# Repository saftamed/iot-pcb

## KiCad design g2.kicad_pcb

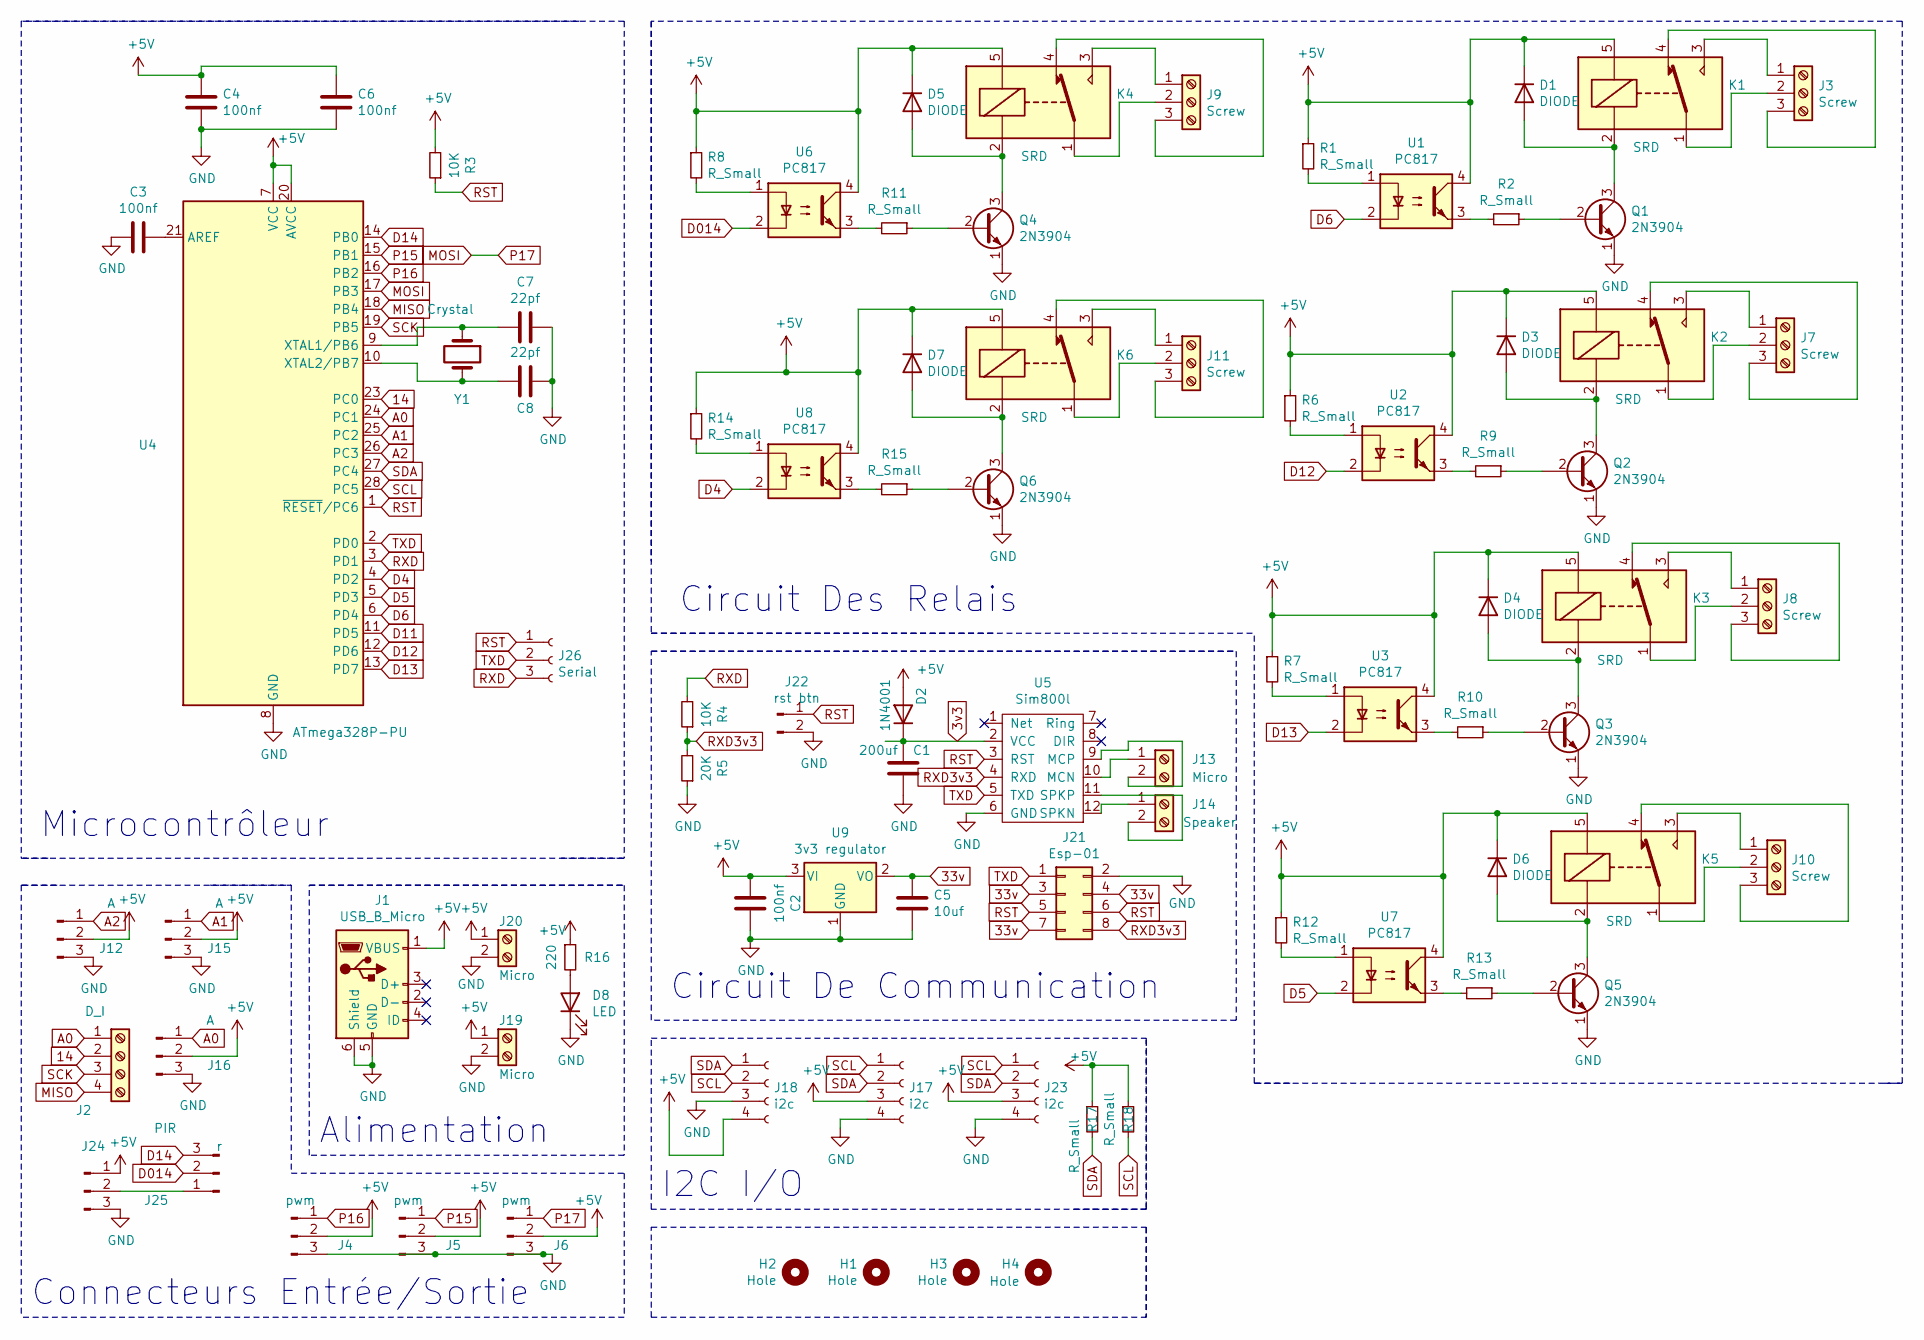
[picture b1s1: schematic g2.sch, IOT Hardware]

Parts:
C1: 200uf; CP_Radial_D5.0mm_P2.50mm
C2, C3, C4, C6: 100nf; C_Disc_D5.0mm_W2.5mm_P2.50mm
C5: 10uf; CP_Radial_D5.0mm_P2.50mm
C7, C8: 22pf; C_Disc_D5.0mm_W2.5mm_P2.50mm
D1, D3, D4, D5, D6, D7: DIODE; D_DO-41_SOD81_P7.62mm_Horizontal
D2: 1N4001; D_DO-41_SOD81_P7.62mm_Horizontal
D8: LED; LED_D3.0mm
H1, H2, H3, H4: Hole; MountingHole_2.7mm_M2.5_Pad_Via
J1: USB_B_Micro; USB_Micro-B_Molex_47346-0001
J2: D_I; TerminalBlock_bornier-4_P5.08mm
J3, J7, J8, J9, J10, J11: Screw; TerminalBlock_bornier-3_P5.08mm
J4, J5, J6: pwm; PinHeader_1x03_P2.54mm_Vertical
J12, J15, J16: A; PinHeader_1x03_P2.54mm_Vertical
J13, J19, J20: Micro; TerminalBlock_bornier-2_P5.08mm
J14: Speaker; TerminalBlock_bornier-2_P5.08mm
J17, J18, J23: i2c; PinSocket_1x04_P2.54mm_Vertical
J21: Esp-01; PinSocket_2x04_P2.54mm_Vertical
J22: rst btn; PinHeader_1x02_P2.54mm_Vertical
J24: PIR; PinHeader_1x03_P2.54mm_Vertical
J25: r; PinHeader_1x03_P2.54mm_Vertical
J26: Serial; PinSocket_1x03_P2.54mm_Vertical
K1, K2, K3, K4, K5, K6: SRD; Relay_SPDT_SANYOU_SRD_Series_Form_C
Q1, Q2, Q3, Q4, Q5, Q6: 2N3904; TO-92_Inline
R1, R2, R6, R7, R8, R9, R10, R11, R12, R13, R14, R15, R17, R18: R_Small; R_Axial_DIN0204_L3.6mm_D1.6mm_P5.08mm_Horizontal
R3, R4: 10K; R_Axial_DIN0204_L3.6mm_D1.6mm_P5.08mm_Horizontal
R5: 20K; R_Axial_DIN0204_L3.6mm_D1.6mm_P5.08mm_Horizontal
R16: 220; R_Axial_DIN0204_L3.6mm_D1.6mm_P5.08mm_Horizontal
U1, U2, U3, U6, U7, U8: PC817; DIP-4_W7.62mm
U4: ATmega328P-PU; DIP-28_W7.62mm
U5: Sim800l; sim800l
U9: 3v3 regulator; SOT-223-3_TabPin2
Y1: Crystal; Crystal_HC18-U_Vertical

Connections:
3v3: C1.1, D2.1 (K), U5.2 (VCC)
14: J2.2, U4.23 (PC0)
33v: C5.1, J21.3, J21.4, J21.7, U9.2 (VO)
+5V: C2.2, C4.1, C6.1, D1.2 (K), D2.2 (A), D3.2 (K), D4.2 (K), D5.2 (K), D6.2 (K), D7.2 (K), J1.1 (VBUS), J4.2, J5.2, J6.2, J12.2, J15.2, J16.2, J17.3, J18.4, J19.1, J20.1, J23.3, J24.1, K1.5, K2.5, K3.5, K4.5, K5.5, K6.5, R1.1, R3.2, R6.1, R7.1, R8.1, R12.1, R14.1, R16.1, R17.1, R18.1, U1.4, U2.4, U3.4, U4.7 (VCC), U4.20 (AVCC), U6.4, U7.4, U8.4, U9.3 (VI); also elsewhere on the board
A0: J2.1, J16.1, U4.24 (PC1)
A1: J15.1, U4.25 (PC2)
A2: J12.1, U4.26 (PC3)
D4: U4.4 (PD2), U8.2
D5: U4.5 (PD3), U7.2
D6: U1.2, U4.6 (PD4)
D11: U4.11 (PD5)
D12: U2.2, U4.12 (PD6)
D13: U3.2, U4.13 (PD7)
D014: J25.2, U6.2
D14: J25.3, U4.14 (PB0)
GND: C1.2, C2.1, C3.2, C4.2, C5.2, C6.2, C7.1, C8.1, D8.1 (K), J1.5 (GND), J1.6 (Shield), J4.3, J5.3, J6.3, J12.3, J15.3, J16.3, J17.4, J18.3, J19.2, J20.2, J21.2, J22.2, J23.4, J24.3, Q1.1 (E), Q2.1 (E), Q3.1 (E), Q4.1 (E), Q5.1 (E), Q6.1 (E), R5.1, U4.8 (GND), U4.22 (GND), U5.6 (GND), U9.1 (GND); also elsewhere on the board
MISO: J2.4, U4.18 (PB4)
MOSI: J6.1, U4.17 (PB3)
unnamed: C3.1, U4.21 (AREF)
unnamed: C7.2, U4.9 (XTAL1/PB6), Y1.1
unnamed: C8.2, U4.10 (XTAL2/PB7), Y1.2
unnamed: D1.1 (A), K1.2, Q1.3 (C)
unnamed: D3.1 (A), K2.2, Q2.3 (C)
unnamed: D4.1 (A), K3.2, Q3.3 (C)
unnamed: D5.1 (A), K4.2, Q4.3 (C)
unnamed: D6.1 (A), K5.2, Q5.3 (C)
unnamed: D7.1 (A), K6.2, Q6.3 (C)
unnamed: D8.2 (A), R16.2
unnamed: J3.1, K1.3
unnamed: J3.2, K1.1
unnamed: J3.3, K1.4
unnamed: J7.1, K2.3
unnamed: J7.2, K2.1
unnamed: J7.3, K2.4
unnamed: J8.1, K3.3
unnamed: J8.2, K3.1
unnamed: J8.3, K3.4
unnamed: J9.1, K4.3
unnamed: J9.2, K4.1
unnamed: J9.3, K4.4
unnamed: J10.1, K5.3
unnamed: J10.2, K5.1
unnamed: J10.3, K5.4
unnamed: J11.1, K6.3
unnamed: J11.2, K6.1
unnamed: J11.3, K6.4
unnamed: J13.1, U5.10 (MCN)
unnamed: J13.2, U5.9 (MCP)
unnamed: J14.1, U5.12 (SPKN)
unnamed: J14.2, U5.11 (SPKP)
unnamed: J24.2, J25.1
unnamed: Q1.2 (B), R2.1
unnamed: Q2.2 (B), R9.1
unnamed: Q3.2 (B), R10.1
unnamed: Q4.2 (B), R11.1
unnamed: Q5.2 (B), R13.1
unnamed: Q6.2 (B), R15.1
unnamed: R1.2, U1.1
unnamed: R2.2, U1.3
unnamed: R6.2, U2.1
unnamed: R7.2, U3.1
unnamed: R8.2, U6.1
unnamed: R9.2, U2.3
unnamed: R10.2, U3.3
unnamed: R11.2, U6.3
unnamed: R12.2, U7.1
unnamed: R13.2, U7.3
unnamed: R14.2, U8.1
unnamed: R15.2, U8.3
P15: J5.1, U4.15 (PB1)
P16: J4.1, U4.16 (PB2)
RST: J21.5, J21.6, J22.1, J26.1, R3.1, U4.1 (~RESET~/PC6), U5.3 (RST)
RXD: J26.3, R4.2, U4.3 (PD1)
RXD3v3: J21.8, R4.1, R5.2, U5.4 (RXD)
SCK: J2.3, U4.19 (PB5)
SCL: J17.1, J18.2, J23.1, R18.2, U4.28 (PC5); also elsewhere on the board
SDA: J17.2, J18.1, J23.2, R17.2, U4.27 (PC4); also elsewhere on the board
TXD: J21.1, J26.2, U4.2 (PD0), U5.5 (TXD)

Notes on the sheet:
Connecteurs Entrée/Sortie
Alimentation
I2C I/O
Circuit De Communication
Circuit Des Relais
Microcontrôleur

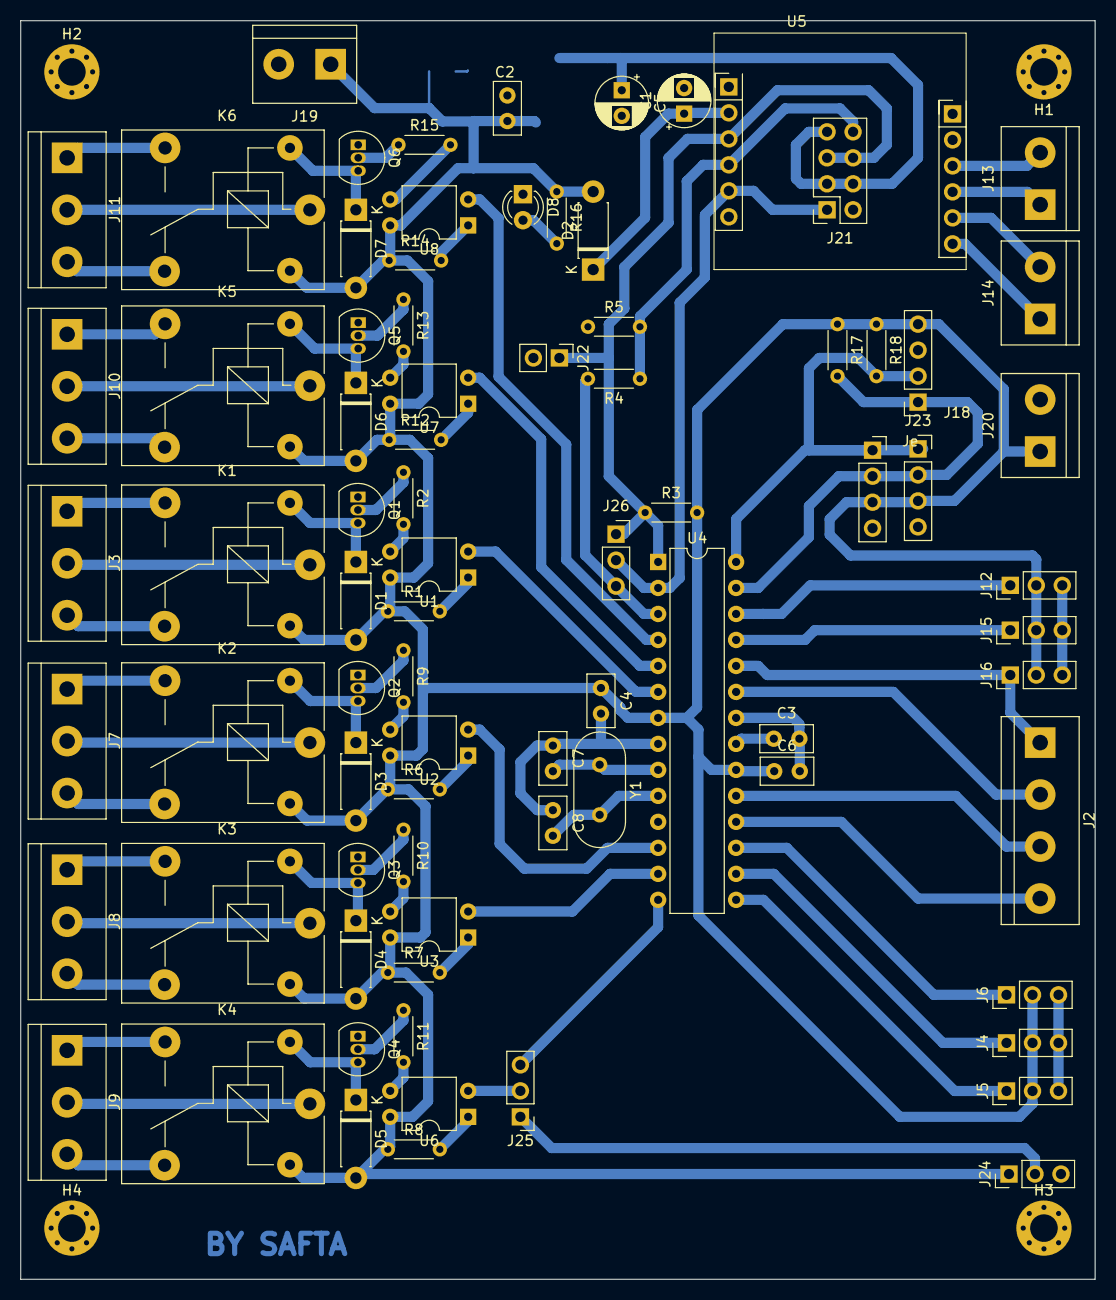
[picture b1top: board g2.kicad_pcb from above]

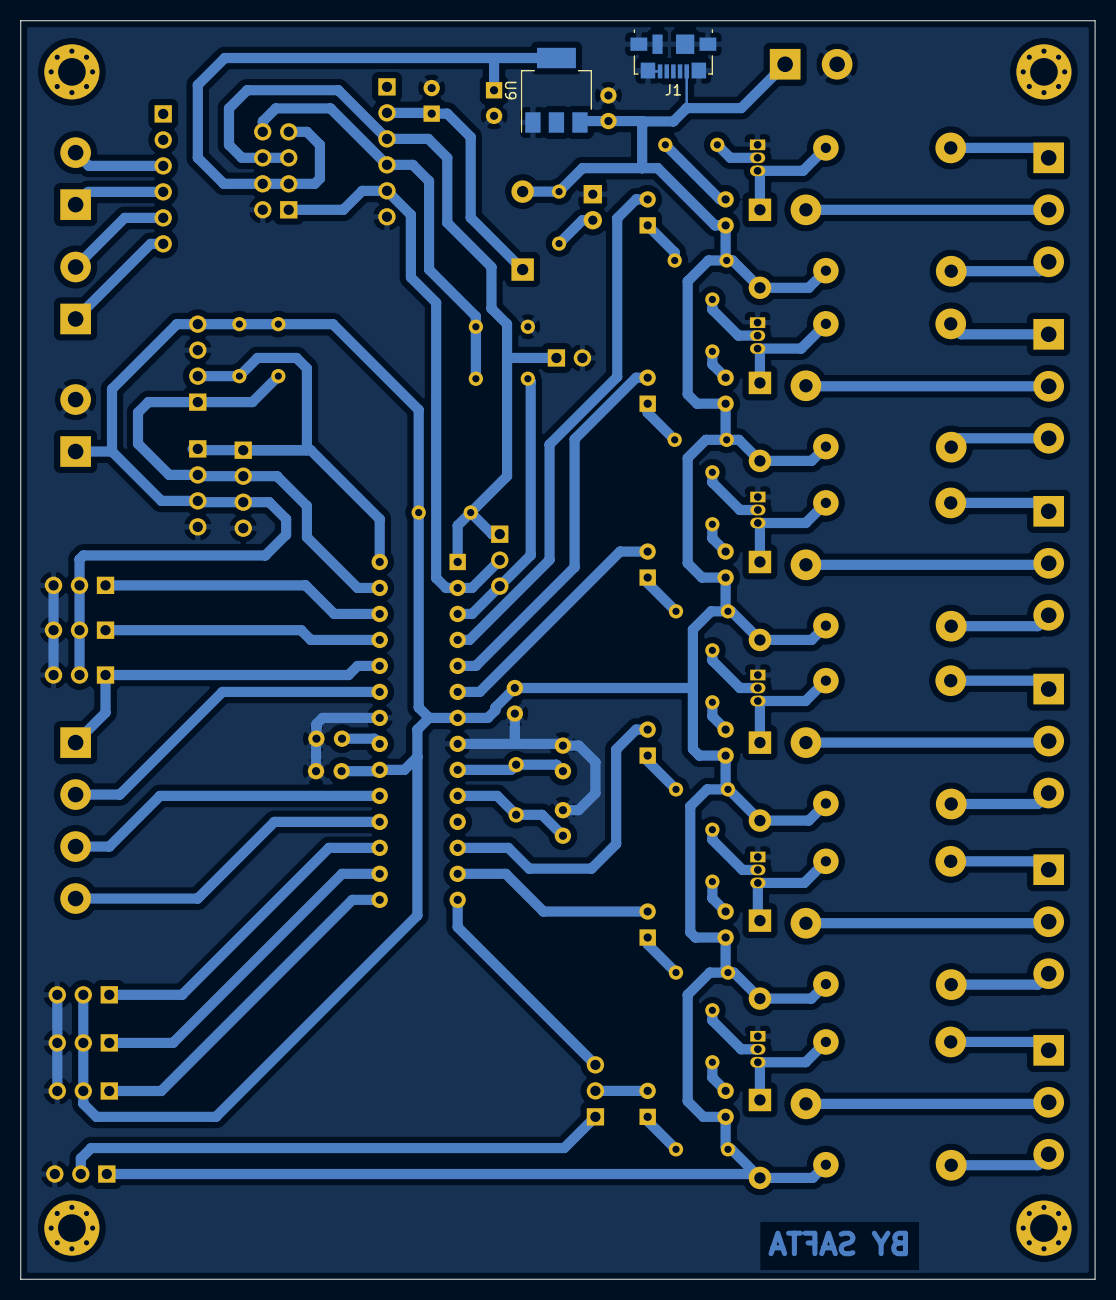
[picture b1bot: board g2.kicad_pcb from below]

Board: 2 copper layers, 105.0 x 123.0 mm, 86 parts (2 on the bottom side), 77 nets.

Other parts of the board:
Je: i2c; PinSocket_1x04_P2.54mm_Vertical

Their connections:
+5V: Je.3; also elsewhere on the board
GND: Je.4; also elsewhere on the board
SCL: Je.1; also elsewhere on the board
SDA: Je.2; also elsewhere on the board

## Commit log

2021-06-15 1.1.0
2021-06-17 1.2.0
2021-06-18 1.3.0
2021-06-18 1.4.0
2021-06-21 2.0.0
2021-06-26 2.2.0
2021-07-05 3.0.0
2021-07-24 with_timer
2021-08-29 final
